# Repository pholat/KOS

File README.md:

KOS
===

Another RepRap controller based on teensylu/printrboard and more. Controller is designed in last developer version of KiCAD EDA, moreover it is compatibile with teensylu 0.8. If you use Marlin, all you need is to choose teensylu board.

Teensylu-lvlup-0.9v125 is licenced under Creative Commons Attribution-ShareAlike 4.0 International 
http://creativecommons.org/licenses/by-sa/4.0/legalcode

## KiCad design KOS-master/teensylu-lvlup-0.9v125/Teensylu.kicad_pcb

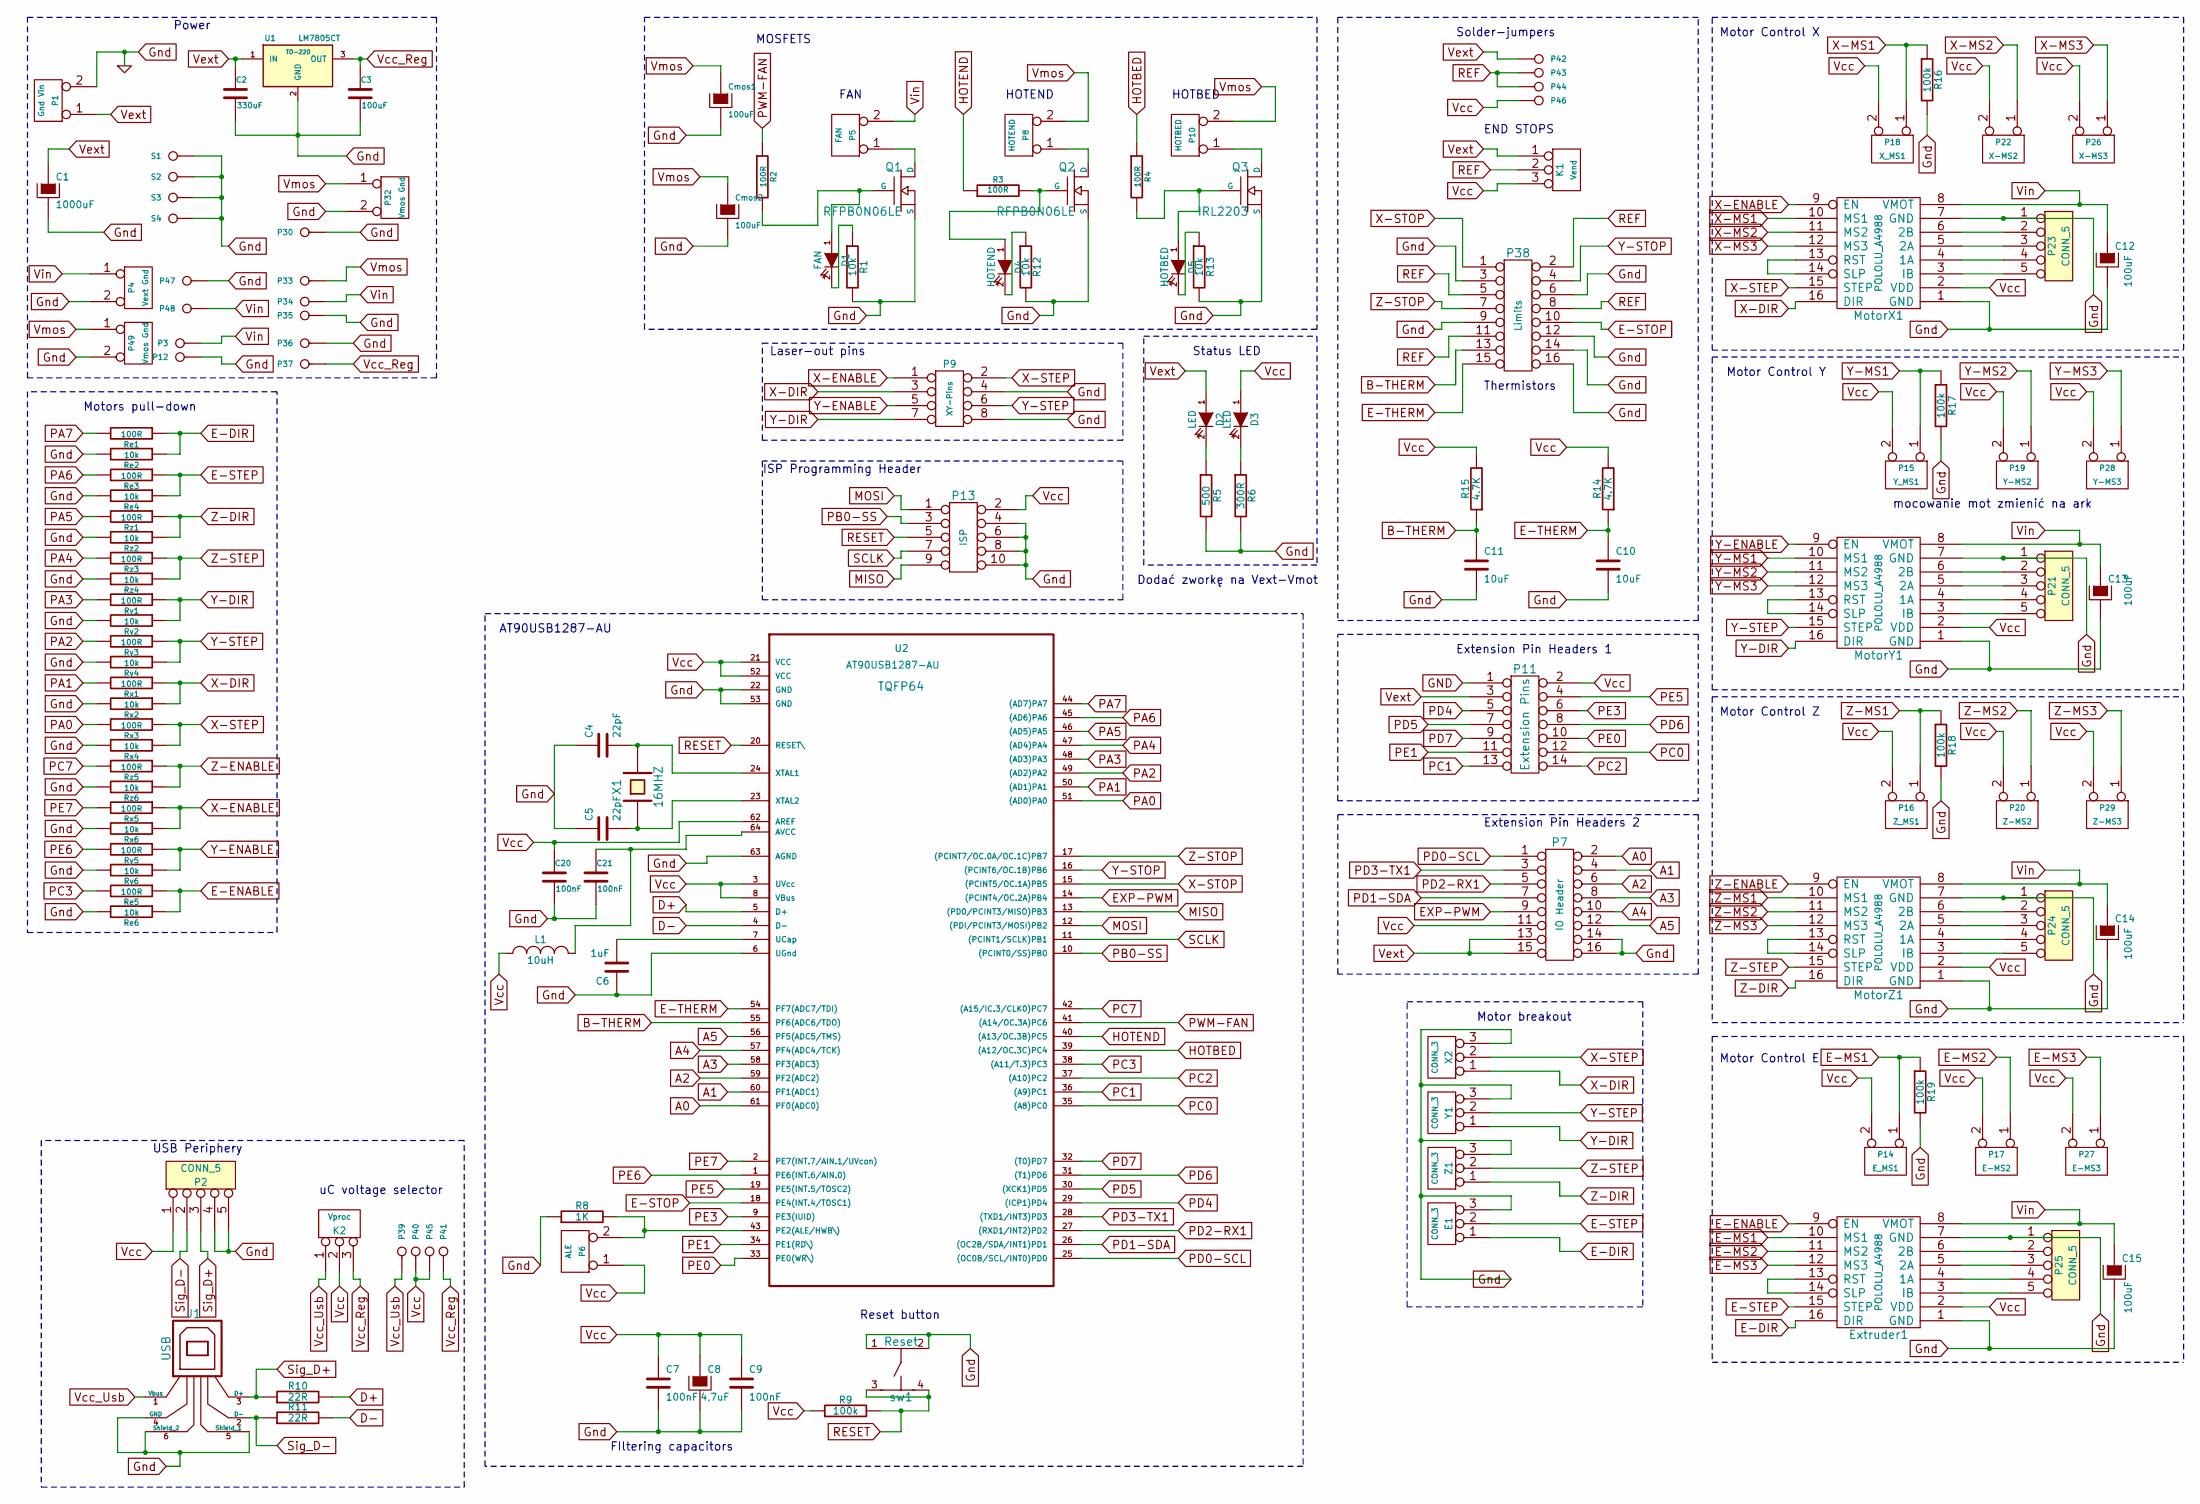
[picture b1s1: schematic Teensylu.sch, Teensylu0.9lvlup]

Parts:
C1: 1000uF
C2: 330uF
C3, C12, C13, C14, C15: 100uF
C4, C5: 22pF
C6: 1uF
C7, C9, C20, C21: 100nF
C8: 4,7uF
C10, C11: 10uF
Cmos1, Cmos2: 100uF
D1: FAN
D2, D3: LED
D4: HOTEND
D5: HOTBED
E1: CONN_3
Extruder1: POLOLU_A4988
J1: USB
K1: Vend
K2: Vproc
L1: 10uH
MotorX1: POLOLU_A4988
MotorY1: POLOLU_A4988
MotorZ1: POLOLU_A4988
P1: Gnd Vin
P2, P21, P23, P24, P25: CONN_5
P3, P34, P47: Vin
P4: Vext Gnd
P5: FAN
P6: ALE
P7: IO Header
P8: HOTEND
P9: XY-Pins
P10: HOTBED
P11: Extension Pins
P12, P30, P35, P36, P48: Gnd
P13: ISP
P14: E_MS1
P15: Y_MS1
P16: Z_MS1
P17: E-MS2
P18: X_MS1
P19: Y-MS2
P20: Z-MS2
P22: X-MS2
P26: X-MS3
P27: E-MS3
P28: Y-MS3
P29: Z-MS3
P32, P49: Vmos Gnd
P33: Vmos
P37: Vreg
P38: Limits
P39, P40, P41, P42, P43, P44, P45, P46: CONN_1
Q1, Q2: RFPB0N06LE
Q3: IRL2203
R1, R12, R13: 10k
R2, R3, R4: 100R
R5: 500
R6: 300R
R8: 1K
R9, R16, R17, R18, R19: 100k
R10, R11: 22R
R14, R15: 4.7K
Re1, Re3, Re5: 100R
Re2, Re4, Re6: 10k
Rx1, Rx3, Rx5: 100R
Rx2, Rx4, Rx6: 10k
Ry1, Ry3, Ry5: 100R
Ry2, Ry4, Ry6: 10k
Rz1, Rz3, Rz5: 100R
Rz2, Rz4, Rz6: 10k
S1, S2, S3, S4: S
U1: LM7805CT; TO-220
U2: AT90USB1287-AU
X1: 16MHZ
X2: CONN_3
Y1: CONN_3
Z1: CONN_3
sw1: Reset

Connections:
A0: P7.2, U2.61 (PF0(ADC0))
A1: P7.4, U2.60 (PF1(ADC1))
A2: P7.6, U2.59 (PF2(ADC2))
A3: P7.8, U2.58 (PF3(ADC3))
A4: P7.10, U2.57 (PF4(ADC4/TCK))
A5: P7.12, U2.56 (PF5(ADC5/TMS))
B-THERM: C11.1, P38.13, R15.1, U2.55 (PF6(ADC6/TDO))
D+: R10.2, U2.5 (D+)
D-: R11.2, U2.4 (D-)
E-DIR: E1.1, Extruder1.16 (DIR), Re1.1, Re2.1
E-ENABLE: Extruder1.9 (EN), Re5.1, Re6.1
E-MS1: Extruder1.10 (MS1), P14.1, R19.1
E-MS2: Extruder1.11 (MS2), P17.1
E-MS3: Extruder1.12 (MS3), P27.1
E-STEP: E1.2 (PM), Extruder1.15 (STEP), Re3.1, Re4.1
E-STOP: P38.10, U2.18 (PE4(INT.4/TOSC1))
E-THERM: C10.1, P38.15, R14.1, U2.54 (PF7(ADC7/TDI))
EXP-PWM: P7.9, U2.14 ((PCINT4/OC.2A)PB4)
GND: C1.2, C2.2, C3.2, C4.1, C5.1, C6.1, C7.2, C8.2, C9.2, C10.2, C11.2, C12.2, C13.2, C14.2, C15.2, C20.2, C21.2, Cmos1.2, Cmos2.2, E1.3, Extruder1.1 (GND), Extruder1.7 (GND), J1.4 (GND), J1.5 (Shield_1), J1.6 (Shield_2), MotorX1.1 (GND), MotorX1.7 (GND), MotorY1.1 (GND), MotorY1.7 (GND), MotorZ1.1 (GND), MotorZ1.7 (GND), P1.2 (PM), P2.4, P2.5, P4.2 (PM), P7.14, P7.16, P9.4, P9.8, P11.1, P12.1, P13.4, P13.6, P13.8, P13.10, P21.1, P23.1, P24.1, P25.1, P30.1, P32.2 (PM), P35.1, P36.1, P38.3, P38.6, P38.9, P38.12, P38.14, P38.16, P47.1, P49.2 (PM), Q1.S, Q2.S, Q3.S, R1.2, R5.2, R6.2, R8.1, R12.2, R13.2, R16.2, R17.2, R18.2, R19.2, Re2.2, Re4.2, Re6.2, Rx2.2, Rx4.2, Rx6.2, Ry2.2, Ry4.2, Ry6.2, Rz2.2, Rz4.2, Rz6.2, S1.1, S2.1, S3.1, S4.1, U1.2 (GND), U2.6 (UGnd), U2.22 (GND), U2.53 (GND), U2.63 (AGND), X2.3, Y1.3, Z1.3, sw1.1, sw1.2
HOTBED: R4.1, U2.39 ((A12/OC.3C)PC4)
HOTEND: R3.1, U2.40 ((A13/OC.3B)PC5)
MISO: P13.9, U2.13 ((PD0/PCINT3/MISO)PB3)
MOSI: P13.1, U2.12 ((PDI/PCINT3/MOSI)PB2)
unnamed: P6.2 (PM), R8.2, U2.43 (PE2(ALE/HWB\))
unnamed: C21.1, L1.2, U2.64 (AVCC)
unnamed: P8.1, Q2.D
unnamed: C6.2, U2.7 (UCap)
unnamed: MotorZ1.13 (RST), MotorZ1.14 (SLP)
unnamed: Extruder1.13 (RST), Extruder1.14 (SLP)
unnamed: P5.1, Q1.D
unnamed: P10.1, Q3.D
unnamed: MotorY1.13 (RST), MotorY1.14 (SLP)
unnamed: D3.2 (K), R6.1
unnamed: MotorX1.13 (RST), MotorX1.14 (SLP)
unnamed: D2.2 (K), R5.1
unnamed: MotorX1.4 (1A), P23.4
unnamed: MotorZ1.3 (IB), P24.5
unnamed: MotorZ1.4 (1A), P24.4
unnamed: MotorZ1.5 (2A), P24.3
unnamed: MotorZ1.6 (2B), P24.2
unnamed: MotorY1.3 (IB), P21.5
unnamed: MotorY1.4 (1A), P21.4
unnamed: MotorY1.5 (2A), P21.3
unnamed: MotorY1.6 (2B), P21.2
unnamed: MotorX1.3 (IB), P23.5
unnamed: MotorX1.5 (2A), P23.3
unnamed: MotorX1.6 (2B), P23.2
unnamed: Extruder1.3 (IB), P25.5
unnamed: Extruder1.4 (1A), P25.4
unnamed: Extruder1.5 (2A), P25.3
unnamed: Extruder1.6 (2B), P25.2
unnamed: D4.1 (A), Q2.G, R3.2
unnamed: D1.1 (A), Q1.G, R2.2
unnamed: D5.2 (K), R13.1
unnamed: D5.1 (A), Q3.G, R4.2
unnamed: D4.2 (K), R12.1
unnamed: D1.2 (K), R1.1
unnamed: C4.2, U2.24 (XTAL1), X1.2
unnamed: C5.2, U2.23 (XTAL2), X1.1
PA0: Rx3.2, U2.51 ((AD0)PA0)
PA1: Rx1.2, U2.50 ((AD1)PA1)
PA2: Ry3.2, U2.49 ((AD2)PA2)
PA3: Ry1.2, U2.48 ((AD3)PA3)
PA4: Rz3.2, U2.47 ((AD4)PA4)
PA5: Rz1.2, U2.46 ((AD5)PA5)
PA6: Re3.2, U2.45 ((AD6)PA6)
PA7: Re1.2, U2.44 ((AD7)PA7)
PB0-SS: P13.3, U2.10 ((PCINT0/SS)PB0)
PC0: P11.12, U2.35 ((A8)PC0)
PC1: P11.13, U2.36 ((A9)PC1)
PC2: P11.14, U2.37 ((A10)PC2)
PC3: Re5.2, U2.38 ((A11/T.3)PC3)
PC7: Rz5.2, U2.42 ((A15/IC.3/CLK0)PC7)
PD0-SCL: P7.1, U2.25 ((OC0B/SCL/INT0)PD0)
PD1-SDA: P7.7, U2.26 ((OC2B/SDA/INT1)PD1)
PD2-RX1: P7.5, U2.27 ((RXD1/INT2)PD2)
PD3-TX1: P7.3, U2.28 ((TXD1/INT3)PD3)
PD4: P11.5, U2.29 ((ICP1)PD4)
PD5: P11.7, U2.30 ((XCK1)PD5)
PD6: P11.8, U2.31 ((T1)PD6)
PD7: P11.9, U2.32 ((T0)PD7)
PE0: P11.10, U2.33 (PE0(WR\))
PE1: P11.11, U2.34 (PE1(RD\))
PE3: P11.6, U2.9 (PE3(IUID))
PE5: P11.4, U2.19 (PE5(INT.5/TOSC2))
PE6: Ry5.2, U2.1 (PE6(INT.6/AIN.0))
PE7: Rx5.2, U2.2 (PE7(INT.7/AIN.1/UVcon))
PWM-FAN: R2.1, U2.41 ((A14/OC.3A)PC6)
REF: K1.2 (PM), P38.2, P38.5, P38.8, P38.11, P43.1, P44.1
RESET: P13.5, R9.2, U2.20 (RESET\), sw1.3, sw1.4
SCLK: P13.7, U2.11 ((PCINT1/SCLK)PB1)
Sig_D+: J1.3 (D+), P2.3, R10.1
Sig_D-: J1.2 (D-), P2.2, R11.1
Vcc: C7.1, C8.1, C9.1, C20.1, D3.1 (A), Extruder1.2 (VDD), K1.3, K2.2 (PM), L1.1, MotorX1.2 (VDD), MotorY1.2 (VDD), MotorZ1.2 (VDD), P2.1, P6.1, P7.11, P11.2, P13.2, P14.2 (PM), P15.2 (PM), P16.2 (PM), P17.2 (PM), P18.2 (PM), P19.2 (PM), P20.2 (PM), P22.2 (PM), P26.2 (PM), P27.2 (PM), P28.2 (PM), P29.2 (PM), P40.1, P45.1, P46.1, R9.1, R14.2, R15.2, U2.3 (UVcc), U2.8 (VBus), U2.21 (VCC), U2.52 (VCC), U2.62 (AREF)
Vcc_Reg: C3.1, K2.3, P37.1, P41.1, U1.3 (OUT)
Vcc_Usb: J1.1 (Vbus), K2.1, P39.1
Vext: C1.1, C2.1, D2.1 (A), K1.1, P1.1, P7.13, P7.15, P11.3, P42.1, U1.1 (IN)
Vin: C12.1, C13.1, C14.1, C15.1, Extruder1.8 (VMOT), MotorX1.8 (VMOT), MotorY1.8 (VMOT), MotorZ1.8 (VMOT), P3.1, P4.1, P5.2 (PM), P34.1, P48.1
Vmos: Cmos1.1, Cmos2.1, P8.2 (PM), P10.2 (PM), P32.1, P33.1, P49.1
X-DIR: MotorX1.16 (DIR), P9.3, Rx1.1, Rx2.1, X2.1
X-ENABLE: MotorX1.9 (EN), P9.1, Rx5.1, Rx6.1
X-MS1: MotorX1.10 (MS1), P18.1, R16.1
X-MS2: MotorX1.11 (MS2), P22.1
X-MS3: MotorX1.12 (MS3), P26.1
X-STEP: MotorX1.15 (STEP), P9.2, Rx3.1, Rx4.1, X2.2 (PM)
X-STOP: P38.1, U2.15 ((PCINT5/OC.1A)PB5)
Y-DIR: MotorY1.16 (DIR), P9.7, Ry1.1, Ry2.1, Y1.1
Y-ENABLE: MotorY1.9 (EN), P9.5, Ry5.1, Ry6.1
Y-MS1: MotorY1.10 (MS1), P15.1, R17.1
Y-MS2: MotorY1.11 (MS2), P19.1
Y-MS3: MotorY1.12 (MS3), P28.1
Y-STEP: MotorY1.15 (STEP), P9.6, Ry3.1, Ry4.1, Y1.2 (PM)
Y-STOP: P38.4, U2.16 ((PCINT6/OC.1B)PB6)
Z-DIR: MotorZ1.16 (DIR), Rz1.1, Rz2.1, Z1.1
Z-ENABLE: MotorZ1.9 (EN), Rz5.1, Rz6.1
Z-MS1: MotorZ1.10 (MS1), P16.1, R18.1
Z-MS2: MotorZ1.11 (MS2), P20.1
Z-MS3: MotorZ1.12 (MS3), P29.1
Z-STEP: MotorZ1.15 (STEP), Rz3.1, Rz4.1, Z1.2 (PM)
Z-STOP: P38.7, U2.17 ((PCINT7/OC.0A/OC.1C)PB7)

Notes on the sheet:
Status LED
ISP Programming Header
Extension Pin Headers 2
MOSFETS
END STOPS
FIltering capacitors
Reset button
Motor Control Y
Motor Control Z
Motor Control E
Motor Control X
Thermistors
Extension Pin Headers 1
AT90USB1287-AU
FAN
HOTEND
HOTBED
Laser-out pins
Solder-jumpers
USB Periphery
uC voltage selector
Motors pull-down
Power
Motor breakout
mocowanie mot zmienić na ark
Dodać zworkę na Vext-Vmot

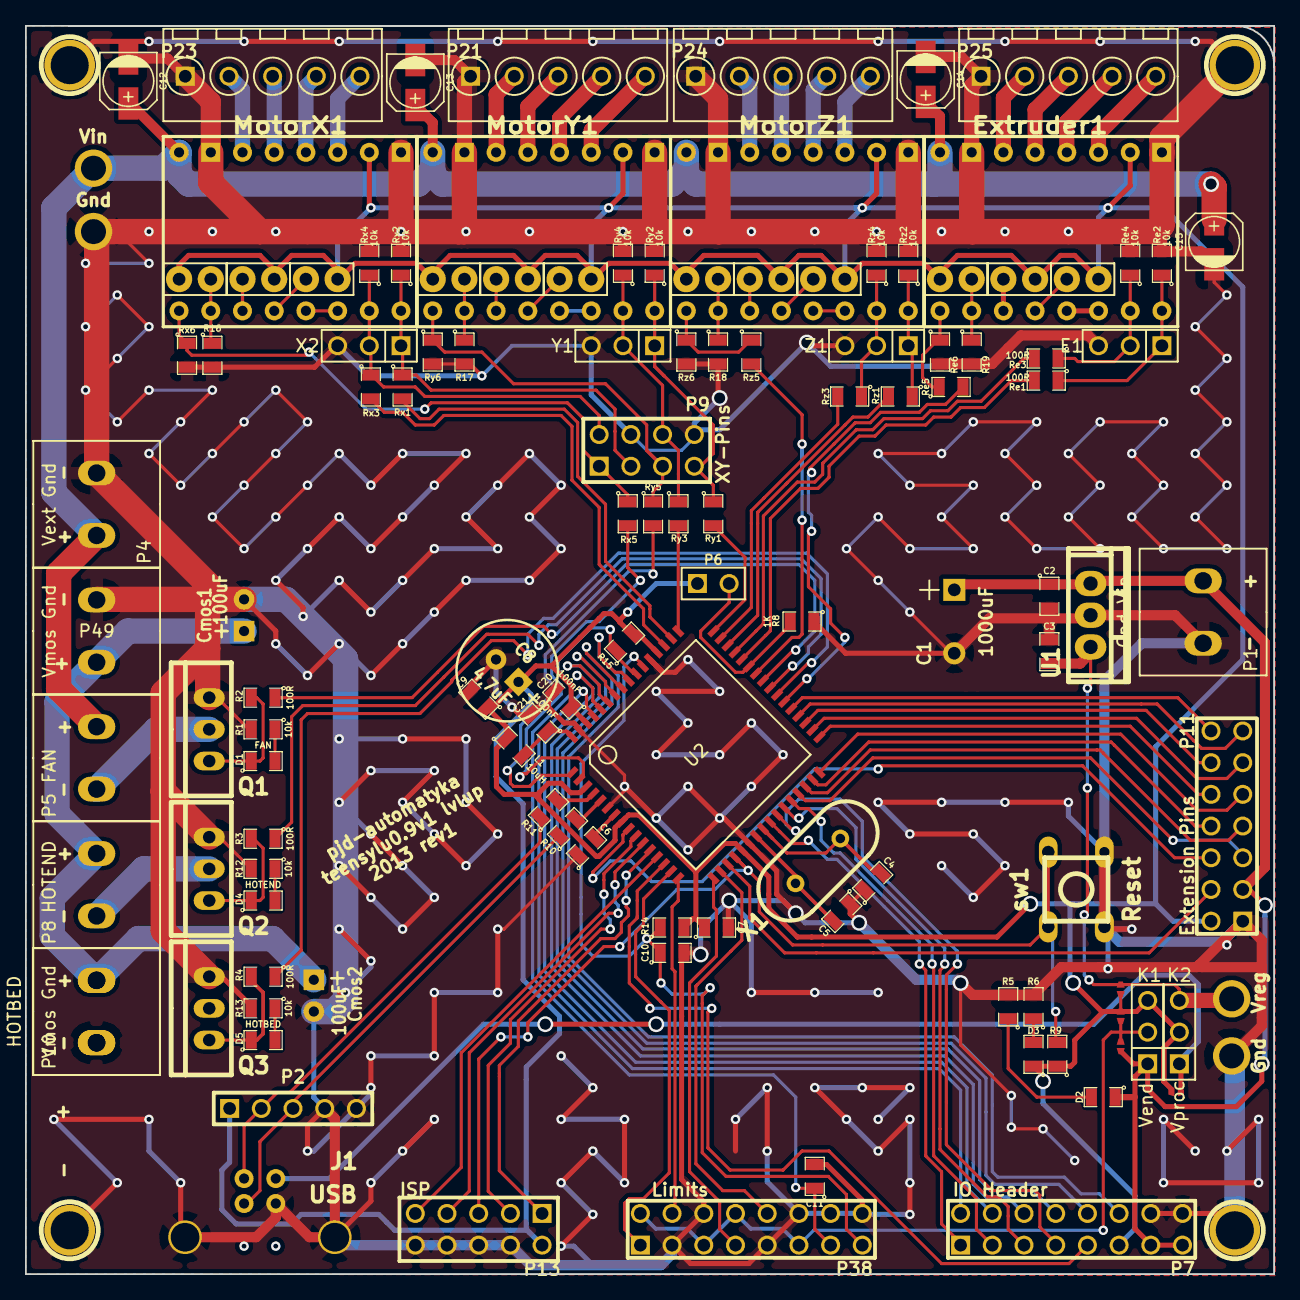
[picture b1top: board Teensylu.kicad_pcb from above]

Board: 2 copper layers, 100.0 x 100.0 mm, 131 parts (0 on the bottom side), 120 nets.

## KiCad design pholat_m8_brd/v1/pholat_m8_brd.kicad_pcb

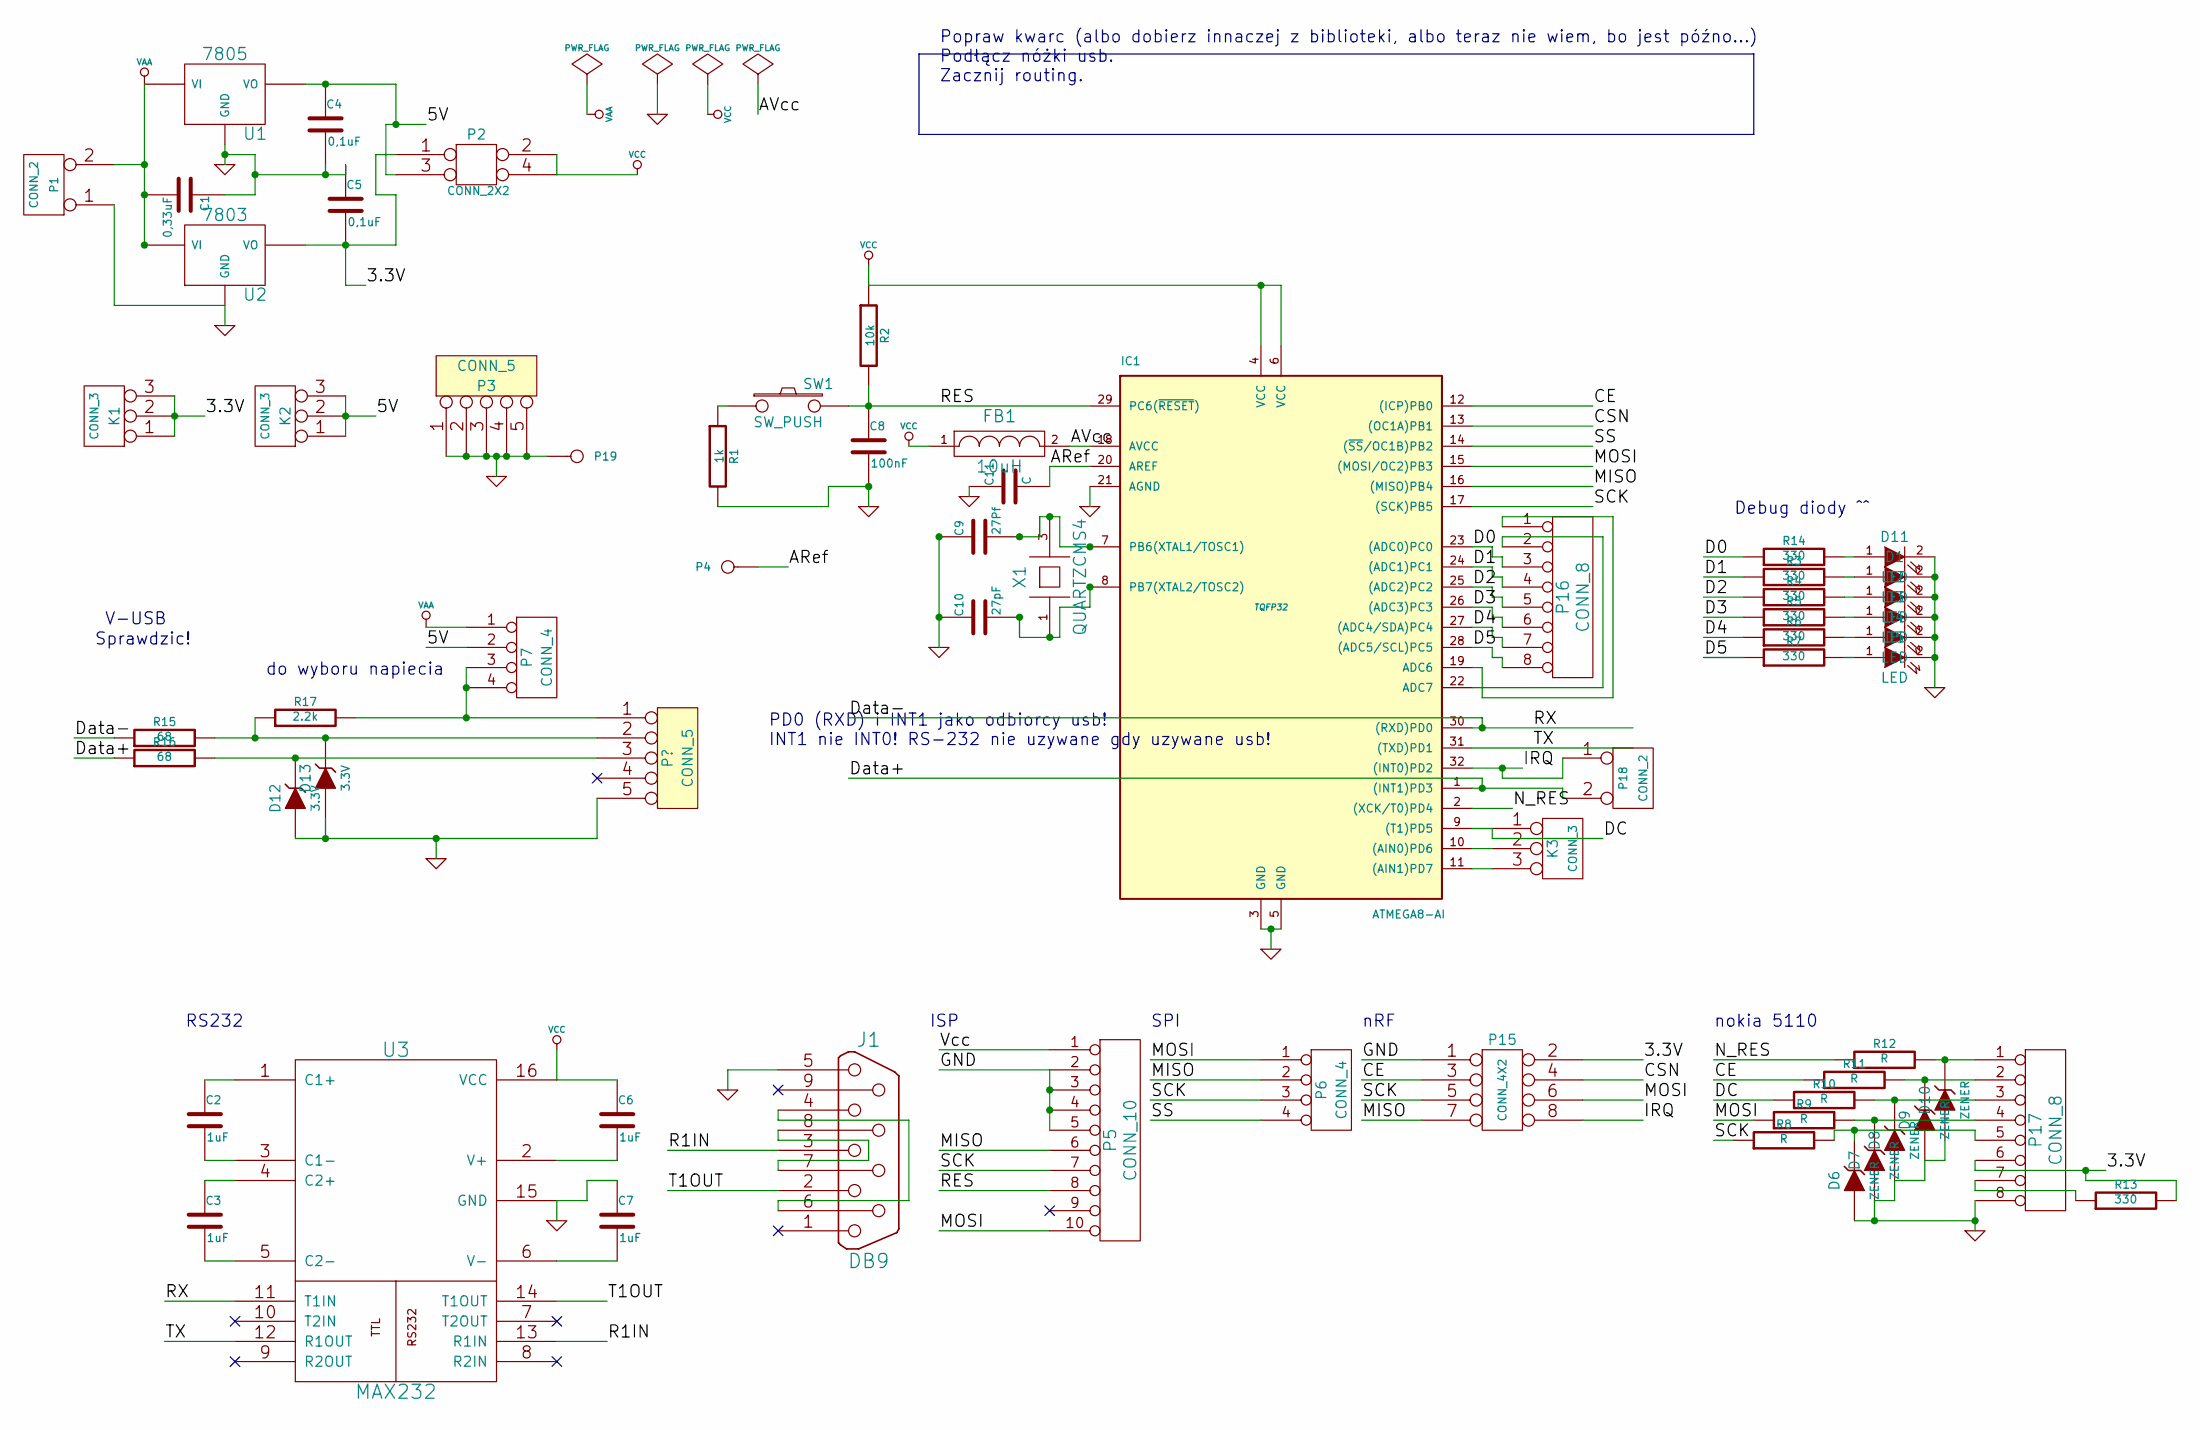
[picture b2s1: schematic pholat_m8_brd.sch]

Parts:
C1: 0,33uF
C2, C3, C6, C7: 1uF
C4, C5: 0,1uF
C8: 100nF
C9: 27Pf
C10: 27pF
C11: C
D1, D2, D3, D4, D5, D11: LED
D6, D7, D8, D9, D10: ZENER
D12, D13: 3.3V
FB1: 10uH
IC1: ATMEGA8-AI; TQFP32
J1: DB9
K1, K2, K3: CONN_3
P1, P18: CONN_2
P2: CONN_2X2
P3: CONN_5
P4, P19: CONN_1
P5: CONN_10
P6, P7: CONN_4
P15: CONN_4X2
P16, P17: CONN_8
R1: 1k
R2: 10k
R3, R4, R5, R6, R7, R13, R14: 330
R8, R9, R10, R11, R12: R
R15, R16: 68
R17: 2.2k
SW1: SW_PUSH
U1: 7805
U2: 7803
U3: MAX232
X1: QUARTZCMS4

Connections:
/3.3V: C5.2, K1.1, K1.2 (PM), K1.3, P2.1, P15.2, P17.6, R13.2, U2.3 (VO)
/5V: C4.1, K2.1, K2.2 (PM), K2.3, P2.3, P7.2, U1.3 (VO)
/ARef: C11.2, IC1.20 (AREF), P4.1
/AVcc: FB1.2, IC1.18 (AVCC)
/CE: IC1.12 ((ICP)PB0), P15.3, R11.1
/CSN: IC1.13 ((OC1A)PB1), P15.4
/D0: IC1.23 ((ADC0)PC0), P16.3, R14.1
/D1: IC1.24 ((ADC1)PC1), P16.4, R3.1
/D2: IC1.25 ((ADC2)PC2), P16.5, R4.1
/D3: IC1.26 ((ADC3)PC3), P16.6, R5.1
/D4: IC1.27 ((ADC4/SDA)PC4), P16.7, R6.1
/D5: IC1.28 ((ADC5/SCL)PC5), P16.8, R7.1
/DC: IC1.9 ((T1)PD5), K3.1, R10.1
/Data+: IC1.1 ((INT1)PD3), P18.2 (PM), R16.1
/Data-: IC1.30 ((RXD)PD0), R15.1, U3.11 (T1IN)
/IRQ: IC1.32 ((INT0)PD2), P15.8, P18.1
/MISO: IC1.16 ((MISO)PB4), P5.6, P6.2, P15.7
/MOSI: IC1.15 ((MOSI/OC2)PB3), P5.10, P6.1, P15.6, R9.1
/N_RES: IC1.2 ((XCK/T0)PD4), R12.1
/R1IN: J1.3, U3.13 (R1IN)
/RES: C8.1, IC1.29 (PC6(~RESET~)), P5.8, R2.2, SW1.2
/SCK: IC1.17 ((SCK)PB5), P5.7, P6.3, P15.5, R8.1
/SS: IC1.14 ((~SS~/OC1B)PB2), P6.4
/T1OUT: J1.2, U3.14 (T1OUT)
/TX: IC1.31 ((TXD)PD1), U3.12 (R1OUT)
GND: C1.1, C4.2, C5.1, C7.1, C8.2, C9.1, C10.1, C11.1, D1.2 (K), D2.2 (K), D3.2 (K), D4.2 (K), D5.2 (K), D6.1 (A), D7.1 (A), D8.1 (A), D9.1 (A), D10.1 (A), D11.2 (K), D12.1 (A), D13.1 (A), IC1.3 (GND), IC1.5 (GND), IC1.21 (AGND), J1.5, P1.1, P3.1, P3.2, P3.3, P3.4, P3.5, P5.2, P5.3, P5.4, P5.5, P15.1, P17.8, P19.1, R1.2, U1.2 (GND), U2.2 (GND), U3.15 (GND); also elsewhere on the board
unnamed: C7.2, U3.6 (V-)
unnamed: C3.2, U3.5 (C2-)
unnamed: C3.1, U3.4 (C2+)
unnamed: C2.2, U3.3 (C1-)
unnamed: C2.1, U3.1 (C1+)
unnamed: D5.1 (A), R7.2
unnamed: D4.1 (A), R6.2
unnamed: D3.1 (A), R5.2
unnamed: D2.1 (A), R4.2
unnamed: D1.1 (A), R3.2
unnamed: J1.7, J1.8
unnamed: J1.4, J1.6
unnamed: C6.2, U3.2 (V+)
unnamed: IC1.19 (ADC6), P16.1
unnamed: IC1.22 (ADC7), P16.2
unnamed: IC1.11 ((AIN1)PD7), K3.3
unnamed: IC1.10 ((AIN0)PD6), K3.2 (PM)
unnamed 43: D13.2 (K), R15.2, R17.1; also elsewhere on the board
unnamed 45: D12.2 (K), R16.2; also elsewhere on the board
unnamed: D11.1 (A), R14.2
unnamed: P17.7, R13.1
unnamed: R1.1, SW1.1
unnamed: D6.2 (K), P17.5, R8.2
unnamed 51: P7.3, P7.4, R17.2; also elsewhere on the board
unnamed: C10.2, IC1.8 (PB7(XTAL2/TOSC2)), X1.1
unnamed: C9.2, IC1.7 (PB6(XTAL1/TOSC1)), X1.3
unnamed: D7.2 (K), P17.4, R9.2
unnamed: D9.2 (K), P17.2, R11.2
unnamed: D8.2 (K), P17.3, R10.2
unnamed: D10.2 (K), P17.1, R12.2
VAA: C1.2, P1.2 (PM), P7.1, U1.1 (VI), U2.1 (VI)
VCC: C6.1, FB1.1, IC1.4 (VCC), IC1.6 (VCC), P2.2, P2.4, P5.1, R2.1, U3.16 (VCC)

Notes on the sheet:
ISP
SPI
nRF
RS232
nokia 5110
V-USB
Sprawdzic!
PD0 (RXD) i INT1 jako odbiorcy usb! INT1 nie INT0! RS-232 nie uzywane gdy uzywane usb!
Debug diody ^^
Popraw kwarc (albo dobierz innaczej z biblioteki, albo teraz nie wiem, bo jest późno...) Podłącz nóżki usb. Zacznij routing.
do wyboru napiecia

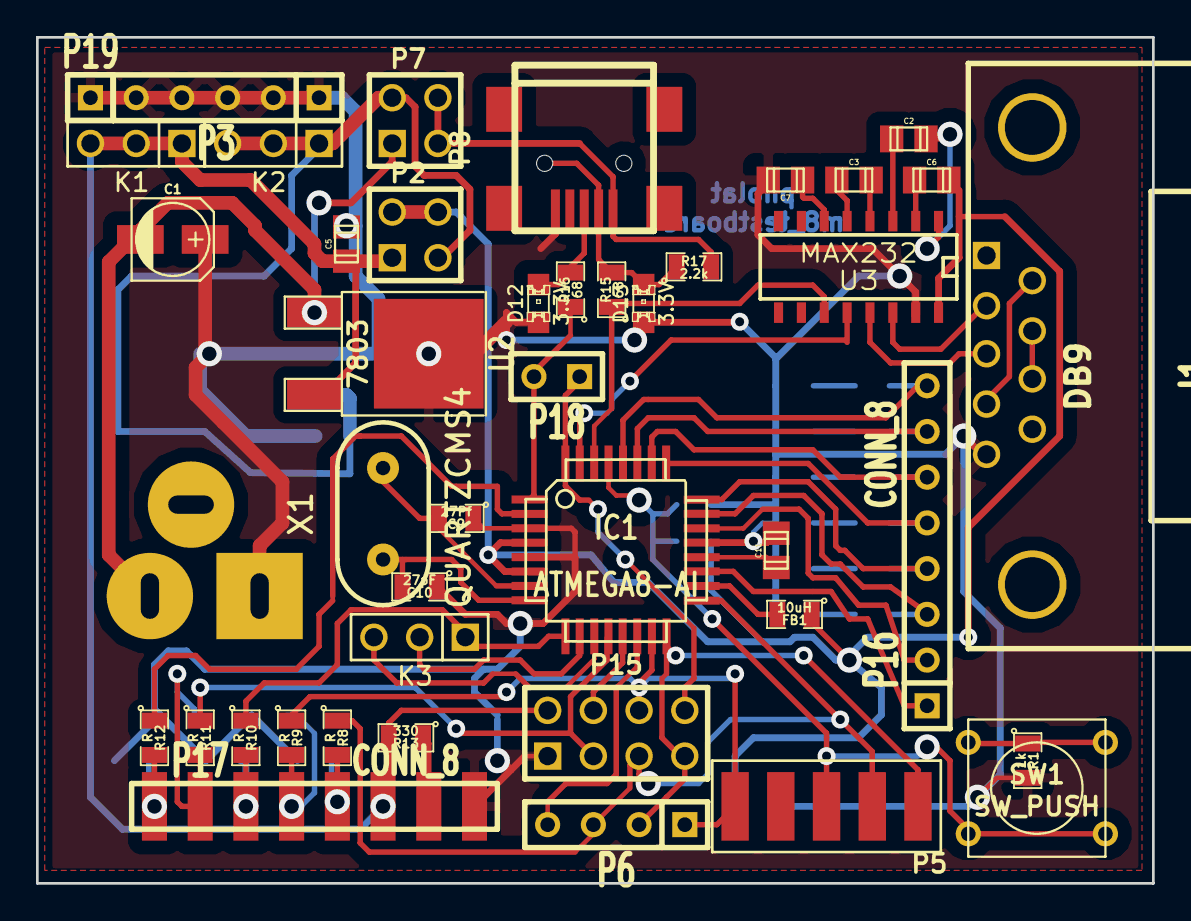
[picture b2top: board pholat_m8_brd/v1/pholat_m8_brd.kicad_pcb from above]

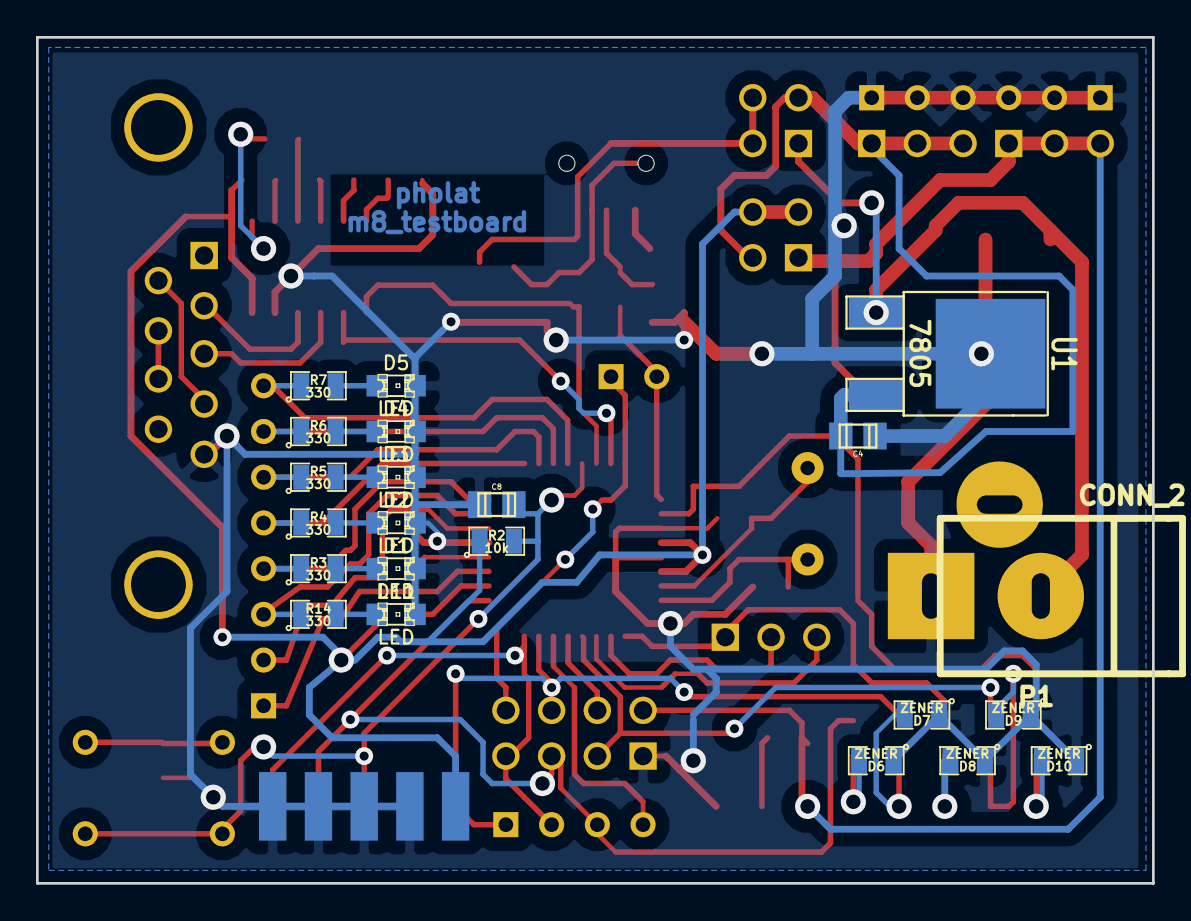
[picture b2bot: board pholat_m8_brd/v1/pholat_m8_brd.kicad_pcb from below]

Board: 2 copper layers, 62.0 x 47.0 mm, 64 parts (22 on the bottom side), 58 nets.

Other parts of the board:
P8: CONN_5; USB_MINI_B

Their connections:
GND: P8.5; also elsewhere on the board
unnamed 43: P8.2; also elsewhere on the board
unnamed 45: P8.3; also elsewhere on the board
unnamed 51: P8.1; also elsewhere on the board

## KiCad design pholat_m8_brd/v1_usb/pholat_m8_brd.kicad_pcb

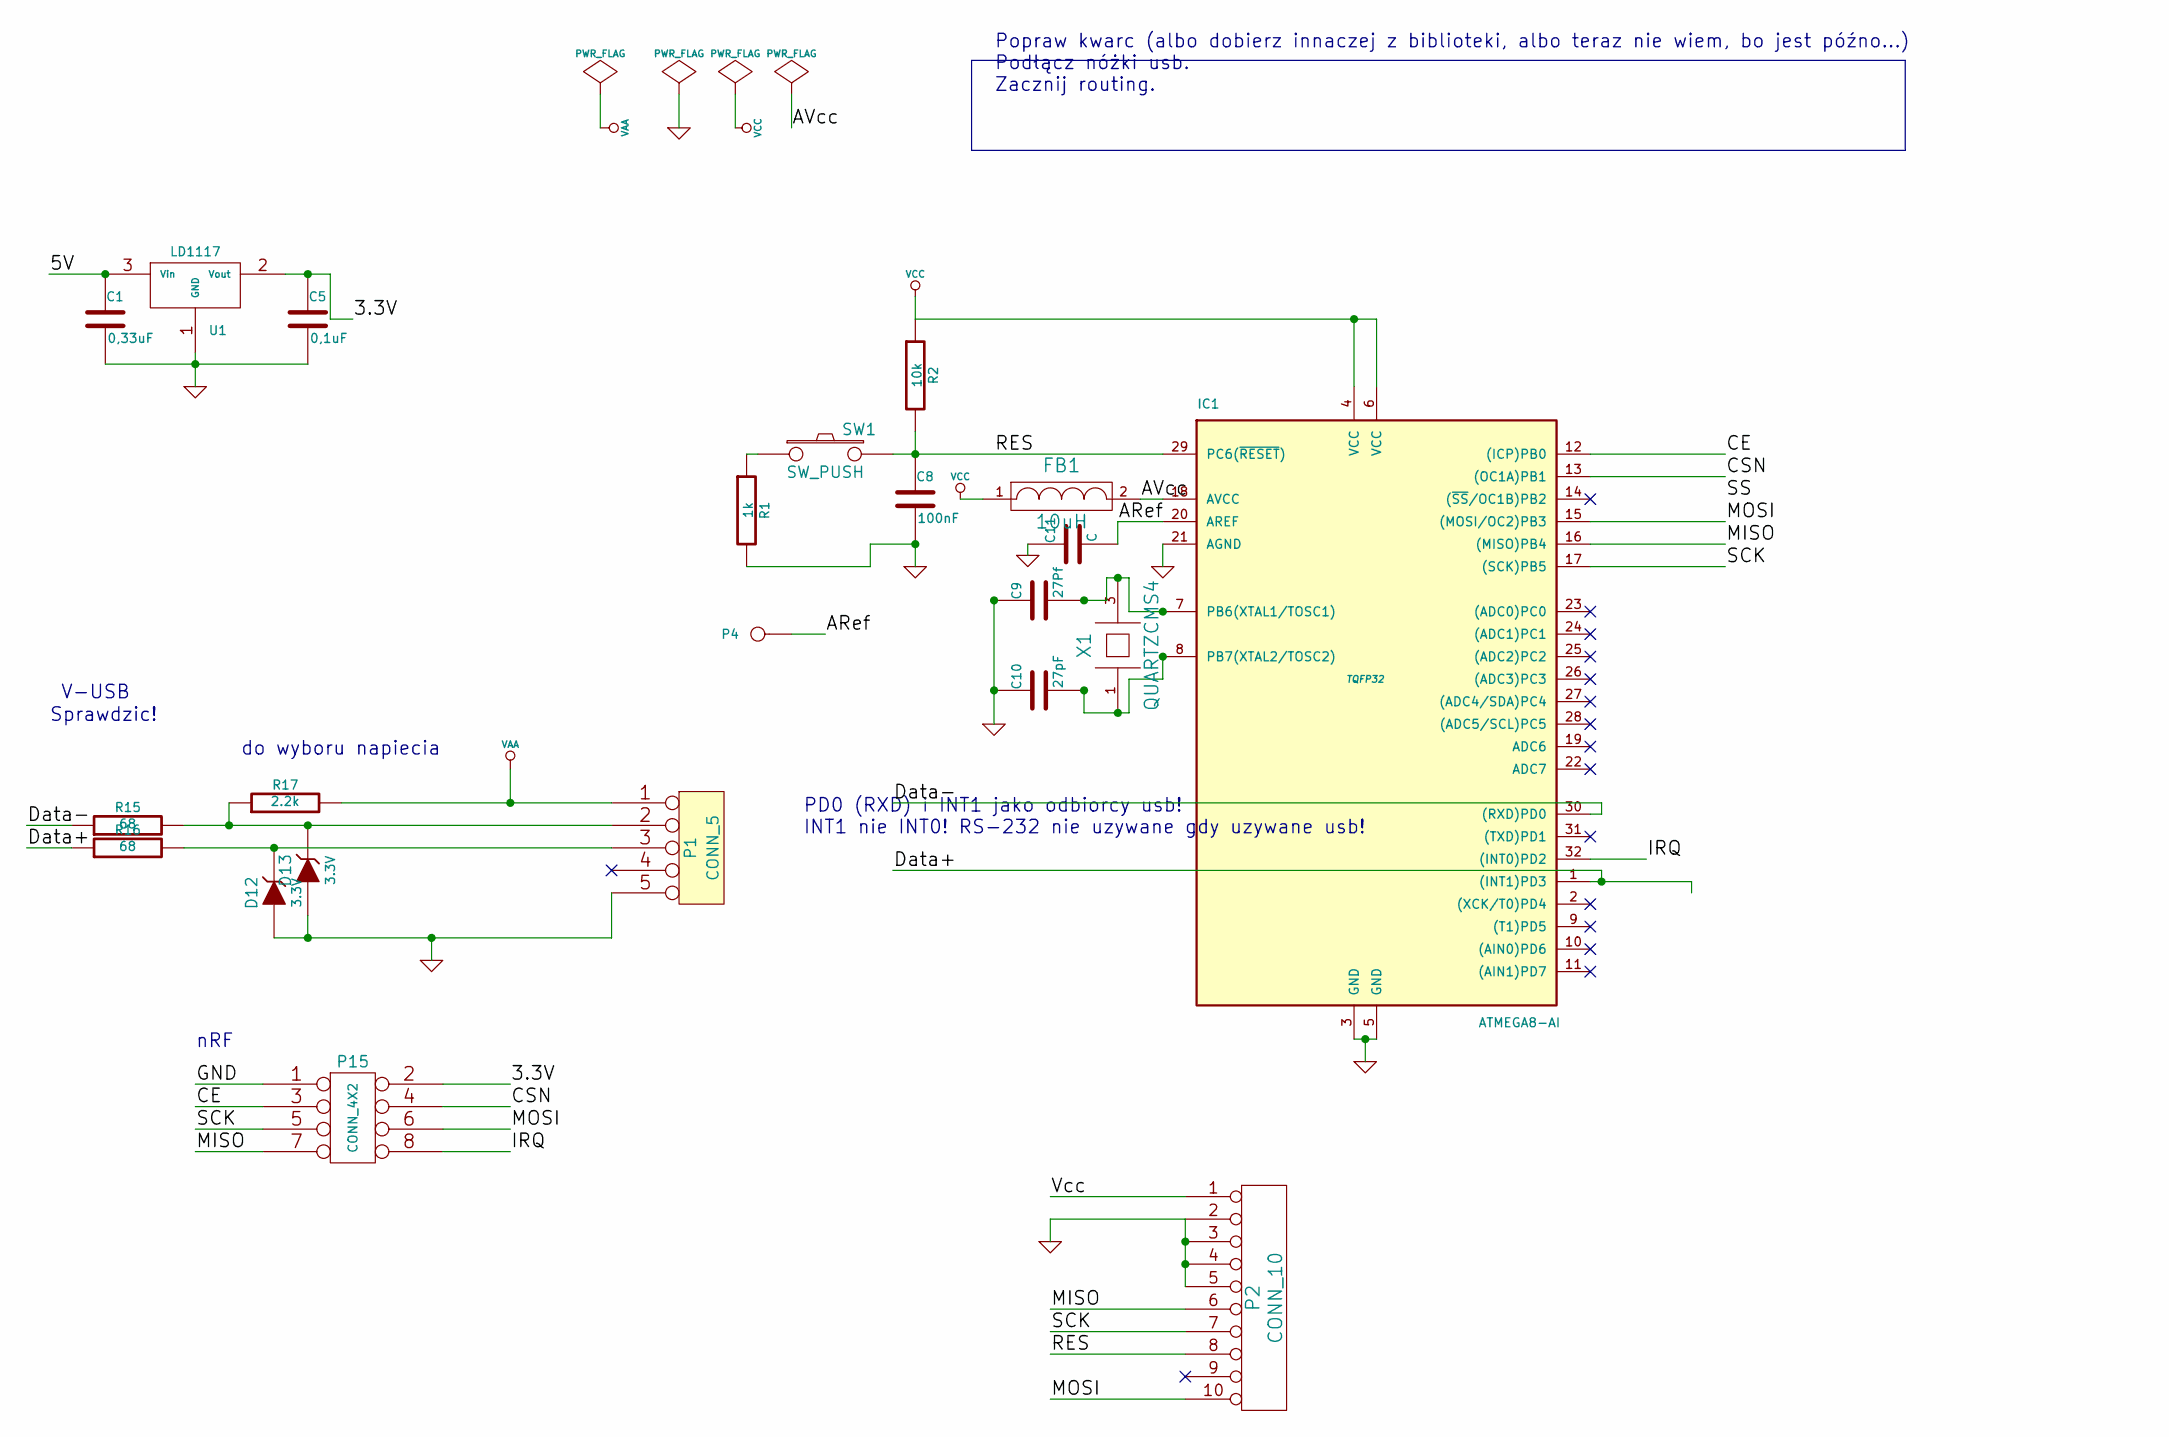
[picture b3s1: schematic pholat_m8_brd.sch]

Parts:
C1: 0,33uF
C5: 0,1uF
C8: 100nF
C9: 27Pf
C10: 27pF
C11: C
D12, D13: 3.3V
FB1: 10uH
IC1: ATMEGA8-AI; TQFP32
P1: CONN_5
P2: CONN_10
P4: CONN_1
P15: CONN_4X2
R1: 1k
R2: 10k
R15, R16: 68
R17: 2.2k
SW1: SW_PUSH
U1: LD1117
X1: QUARTZCMS4

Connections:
/3.3V: C5.1, P15.2, U1.2 (Vout)
/5V: C1.1, U1.3 (Vin)
/ARef: C11.2, IC1.20 (AREF), P4.1
/AVcc: FB1.2, IC1.18 (AVCC)
/CE: IC1.12 ((ICP)PB0), P15.3
/CSN: IC1.13 ((OC1A)PB1), P15.4
/Data+: IC1.1 ((INT1)PD3), R16.1
/Data-: IC1.30 ((RXD)PD0), R15.1
/IRQ: IC1.32 ((INT0)PD2), P15.8
/MISO: IC1.16 ((MISO)PB4), P2.6, P15.7
/MOSI: IC1.15 ((MOSI/OC2)PB3), P2.10, P15.6
/RES: C8.1, IC1.29 (PC6(~RESET~)), P2.8, R2.2, SW1.2
/SCK: IC1.17 ((SCK)PB5), P2.7, P15.5
GND: C1.2, C5.2, C8.2, C9.1, C10.1, C11.1, D12.1 (A), D13.1 (A), IC1.3 (GND), IC1.5 (GND), IC1.21 (AGND), P1.5, P2.2, P2.3, P2.4, P2.5, P15.1, R1.2, U1.1 (GND)
unnamed: C9.2, IC1.7 (PB6(XTAL1/TOSC1)), X1.3
unnamed: C10.2, IC1.8 (PB7(XTAL2/TOSC2)), X1.1
unnamed: R1.1, SW1.1
unnamed: D12.2 (K), P1.3, R16.2
unnamed: D13.2 (K), P1.2, R15.2, R17.1
VAA: P1.1, R17.2
VCC: FB1.1, IC1.4 (VCC), IC1.6 (VCC), P2.1, R2.1

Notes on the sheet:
nRF
V-USB
Sprawdzic!
PD0 (RXD) i INT1 jako odbiorcy usb! INT1 nie INT0! RS-232 nie uzywane gdy uzywane usb!
Popraw kwarc (albo dobierz innaczej z biblioteki, albo teraz nie wiem, bo jest późno...) Podłącz nóżki usb. Zacznij routing.
do wyboru napiecia

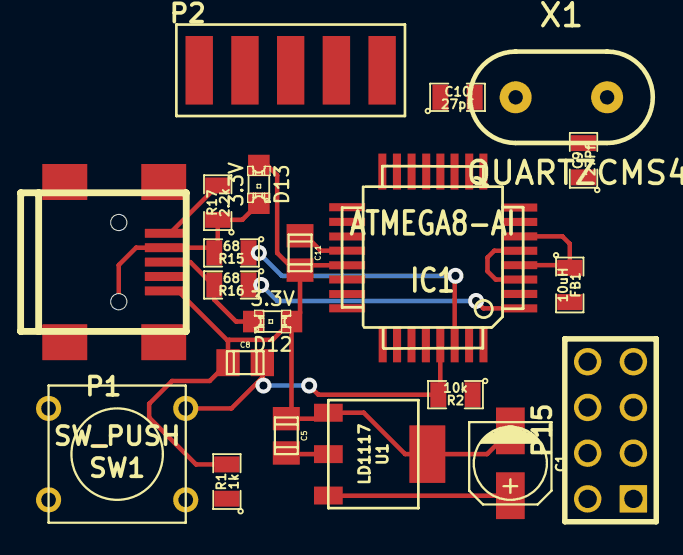
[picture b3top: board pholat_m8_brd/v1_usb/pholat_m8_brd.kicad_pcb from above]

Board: 2 copper layers, 21 parts (0 on the bottom side), 21 nets.

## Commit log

2014-01-07 First upload of last version of teensylu-lvlup.
2014-01-19 My first git - m8 brd 4 {nRF&USB&5510 screen}
2014-02-06 KOS-master lil' remake
